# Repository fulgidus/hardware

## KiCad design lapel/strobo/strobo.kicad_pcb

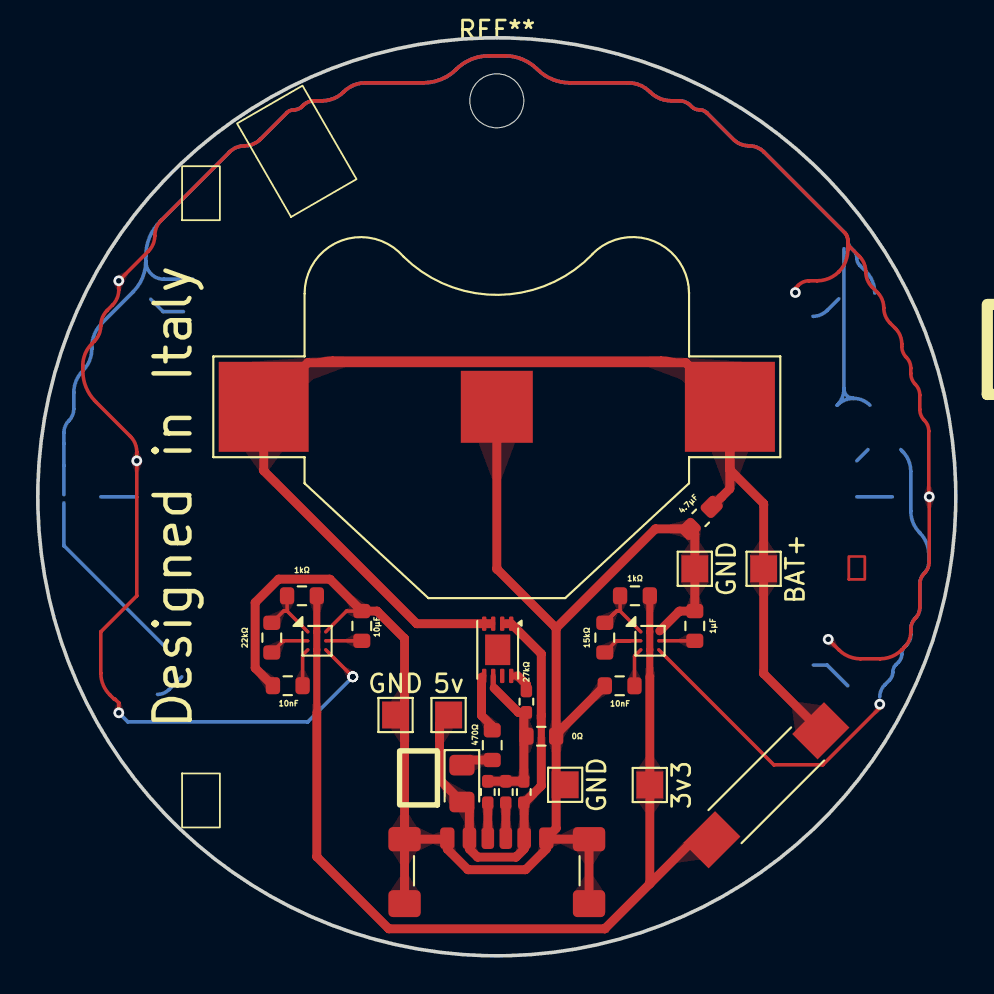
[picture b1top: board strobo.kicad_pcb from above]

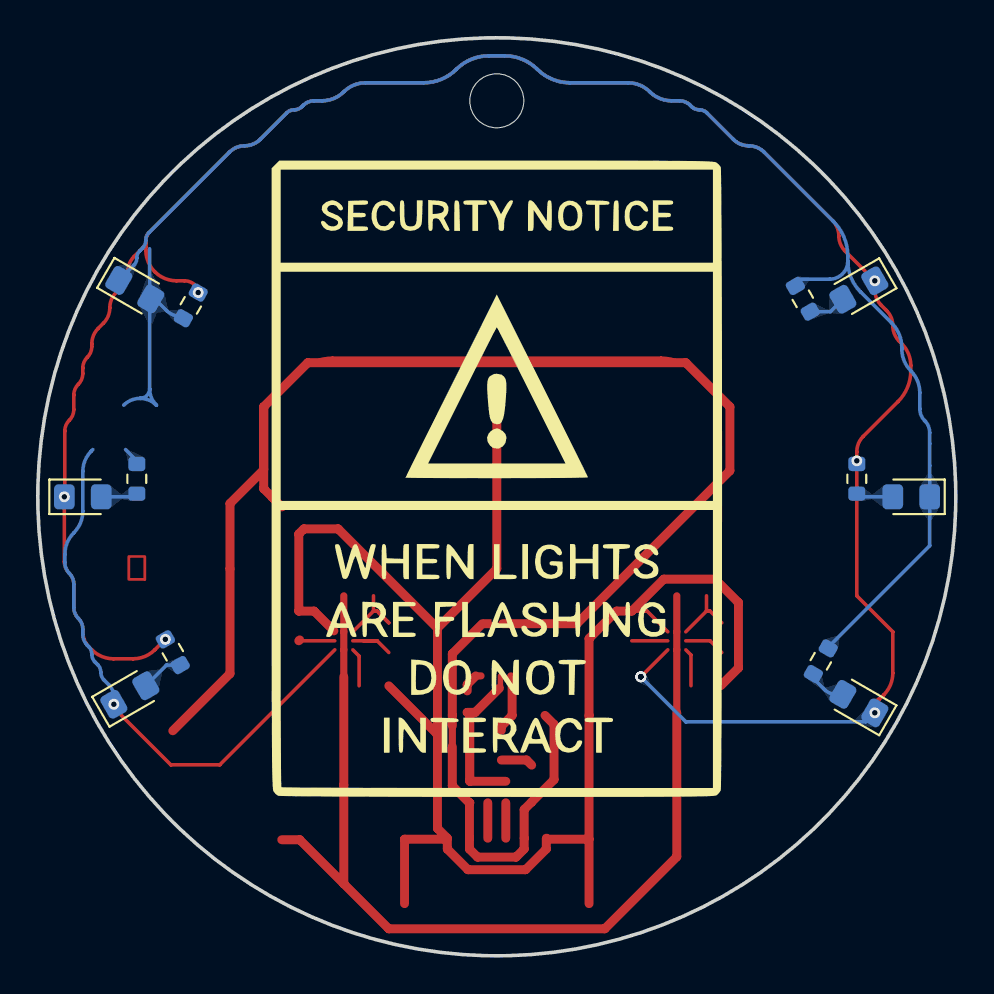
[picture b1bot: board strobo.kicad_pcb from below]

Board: 2 copper layers, 51.0 x 51.0 mm, 35 parts (13 on the bottom side), 25 nets.

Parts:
BT1: 3.7; BatteryHolder_Multicomp_BC-2001_1x2032
B_{1}: 0Ω; R_0603_1608Metric
C1: 4.7µF; R_0402_1005Metric_Pad0.72x0.64mm_HandSolder
C2: 4.7µF; C_0603_1608Metric_Pad1.08x0.95mm_HandSolder
C3: 10µF; R_0603_1608Metric
C4, C6: 10nF; R_0603_1608Metric
C5: 1µF; R_0603_1608Metric
D1, D2, D3, D4, D5, D6, D7: LED; LED_0805_2012Metric_Pad1.15x1.40mm_HandSolder
Image: LOGO
J1: USB-C; USB_C_Receptacle_GCT_USB4135-GF-A_6P_TopMnt_Horizontal
R1, R2: 5.1kΩ; R_0402_1005Metric_Pad0.72x0.64mm_HandSolder
R3: 27kΩ; R_0402_1005Metric_Pad0.72x0.64mm_HandSolder
R4: 470Ω; R_0603_1608Metric
R5, R7, R9, R10, R11, R12, R13, R14: 1kΩ; R_0603_1608Metric
R6: 22kΩ; R_0603_1608Metric
R8: 15kΩ; R_0603_1608Metric
SW1: 0.001; SW_SPST_REED_CT05-XXXX-G1
U2: MCP73831-2-MC; DFN-8-1EP_3x2mm_P0.5mm_EP1.7x1.4mm
U3, U4: LMC555xTP; Texas_DSBGA-8_1.43x1.41mm_Layout3x3_P0.5mm

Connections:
+3.3V: R5.1, R7.1, SW1.2 (B), U3.A2 (VCC), U3.C2 (~RST), U4.A2 (VCC), U4.C2 (~RST)
GND: BT1.2 (-), B_{1}.1, B_{1}.2, C1.1, C2.2, C3.2, C4.1, C5.2, C6.1, J1.A12 (GND), J1.B12 (GND), J1.SH (SHIELD), R1.2, R2.2, R3.1, U2.6 (V_{SS}), U3.A3 (GND), U4.A3 (GND)
unnamed: BT1.1 (+), C2.1, SW1.1 (A), U2.3 (V_{BAT}), U2.4 (V_{BAT})
unnamed: C1.2, D1.2 (A), J1.A9 (VBUS), J1.B9 (VBUS), U2.1 (V_{DD}), U2.2 (V_{DD})
unnamed: D1.1 (K), R4.1
unnamed: D2.2 (A), R9.1
unnamed: D2.1 (K), D4.1 (K), D5.1 (K), R10.2, R13.2, R14.2, U4.C3 (OUT)
unnamed: D3.2 (A), R10.1
unnamed: D3.1 (K), D6.1 (K), D7.1 (K), R9.2, R11.2, R12.2, U3.C3 (OUT)
unnamed: D4.2 (A), R11.1
unnamed: D5.2 (A), R12.1
unnamed: D6.2 (A), R13.1
unnamed: D7.2 (A), R14.1
unnamed: J1.A5 (CC1), R2.1
unnamed: J1.B5 (CC2), R1.1
unnamed: R3.2, U2.8 (PROG)
unnamed: R4.2, U2.5 (STAT)
unnamed: C4.2, U3.C1 (CONT)
unnamed: R5.2, R6.1, U3.A1 (DISCH)
unnamed: R6.2, U3.B1 (THRES)
unnamed: C3.1, U3.B3 (TRIG)
unnamed: C6.2, U4.C1 (CONT)
unnamed: R7.2, R8.1, U4.A1 (DISCH)
unnamed: R8.2, U4.B1 (THRES)
unnamed: C5.1, U4.B3 (TRIG)

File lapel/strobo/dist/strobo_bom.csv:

"Id";"Designator";"Footprint";"Quantity";"Designation";"Supplier and ref";
1;"BT1";"BatteryHolder_Multicomp_BC-2001_1x2032";1;"LIR2032";;;
2;"C1, C2";"C_0805_2012Metric";2;"4.7µF";;;
3;"C3";"C_0805_2012Metric_Pad1.18x1.45mm_HandSolder";1;"10µF";;;
4;"C4, C6";"C_0805_2012Metric_Pad1.18x1.45mm_HandSolder";2;"10nF";;;
5;"C5";"C_0805_2012Metric_Pad1.18x1.45mm_HandSolder";1;"1µF";;;
6;"D1, D2, D3, D4, D5, D6, D7";"LED_0805_2012Metric_Pad1.15x1.40mm_HandSolder";7;"LED";;;
7;"J1";"USB_C_Receptacle_GCT_USB4125-xx-x-0190_6P_TopMnt_Horizontal";1;"USB_C_Receptacle_PowerOnly_6P";;;
8;"R1";"R_0805_2012Metric_Pad1.20x1.40mm_HandSolder";1;"5.1kΩ";;;
9;"R2";"C_0805_2012Metric_Pad1.18x1.45mm_HandSolder";1;"5.1kΩ";;;
10;"R3";"C_0805_2012Metric_Pad1.18x1.45mm_HandSolder";1;"27kΩ";;;
11;"R4, R5, R7, R9, R10, R11, R12, R13, R14";"R_0805_2012Metric_Pad1.20x1.40mm_HandSolder";9;"1kΩ";;;
12;"R6";"R_0805_2012Metric_Pad1.20x1.40mm_HandSolder";1;"22kΩ";;;
13;"R8";"R_0805_2012Metric_Pad1.20x1.40mm_HandSolder";1;"15kΩ";;;
14;"SW1";"SW_Slide_SPDT_Angled_CK_OS102011MA1Q";1;"SW_SPDT";;;
15;"U1";"SOIC-14_3.9x8.7mm_P1.27mm";1;"ICM7556";;;
16;"U2";"DFN-8-1EP_3x2mm_P0.5mm_EP1.7x1.4mm";1;"MCP73831-2-MC";;;

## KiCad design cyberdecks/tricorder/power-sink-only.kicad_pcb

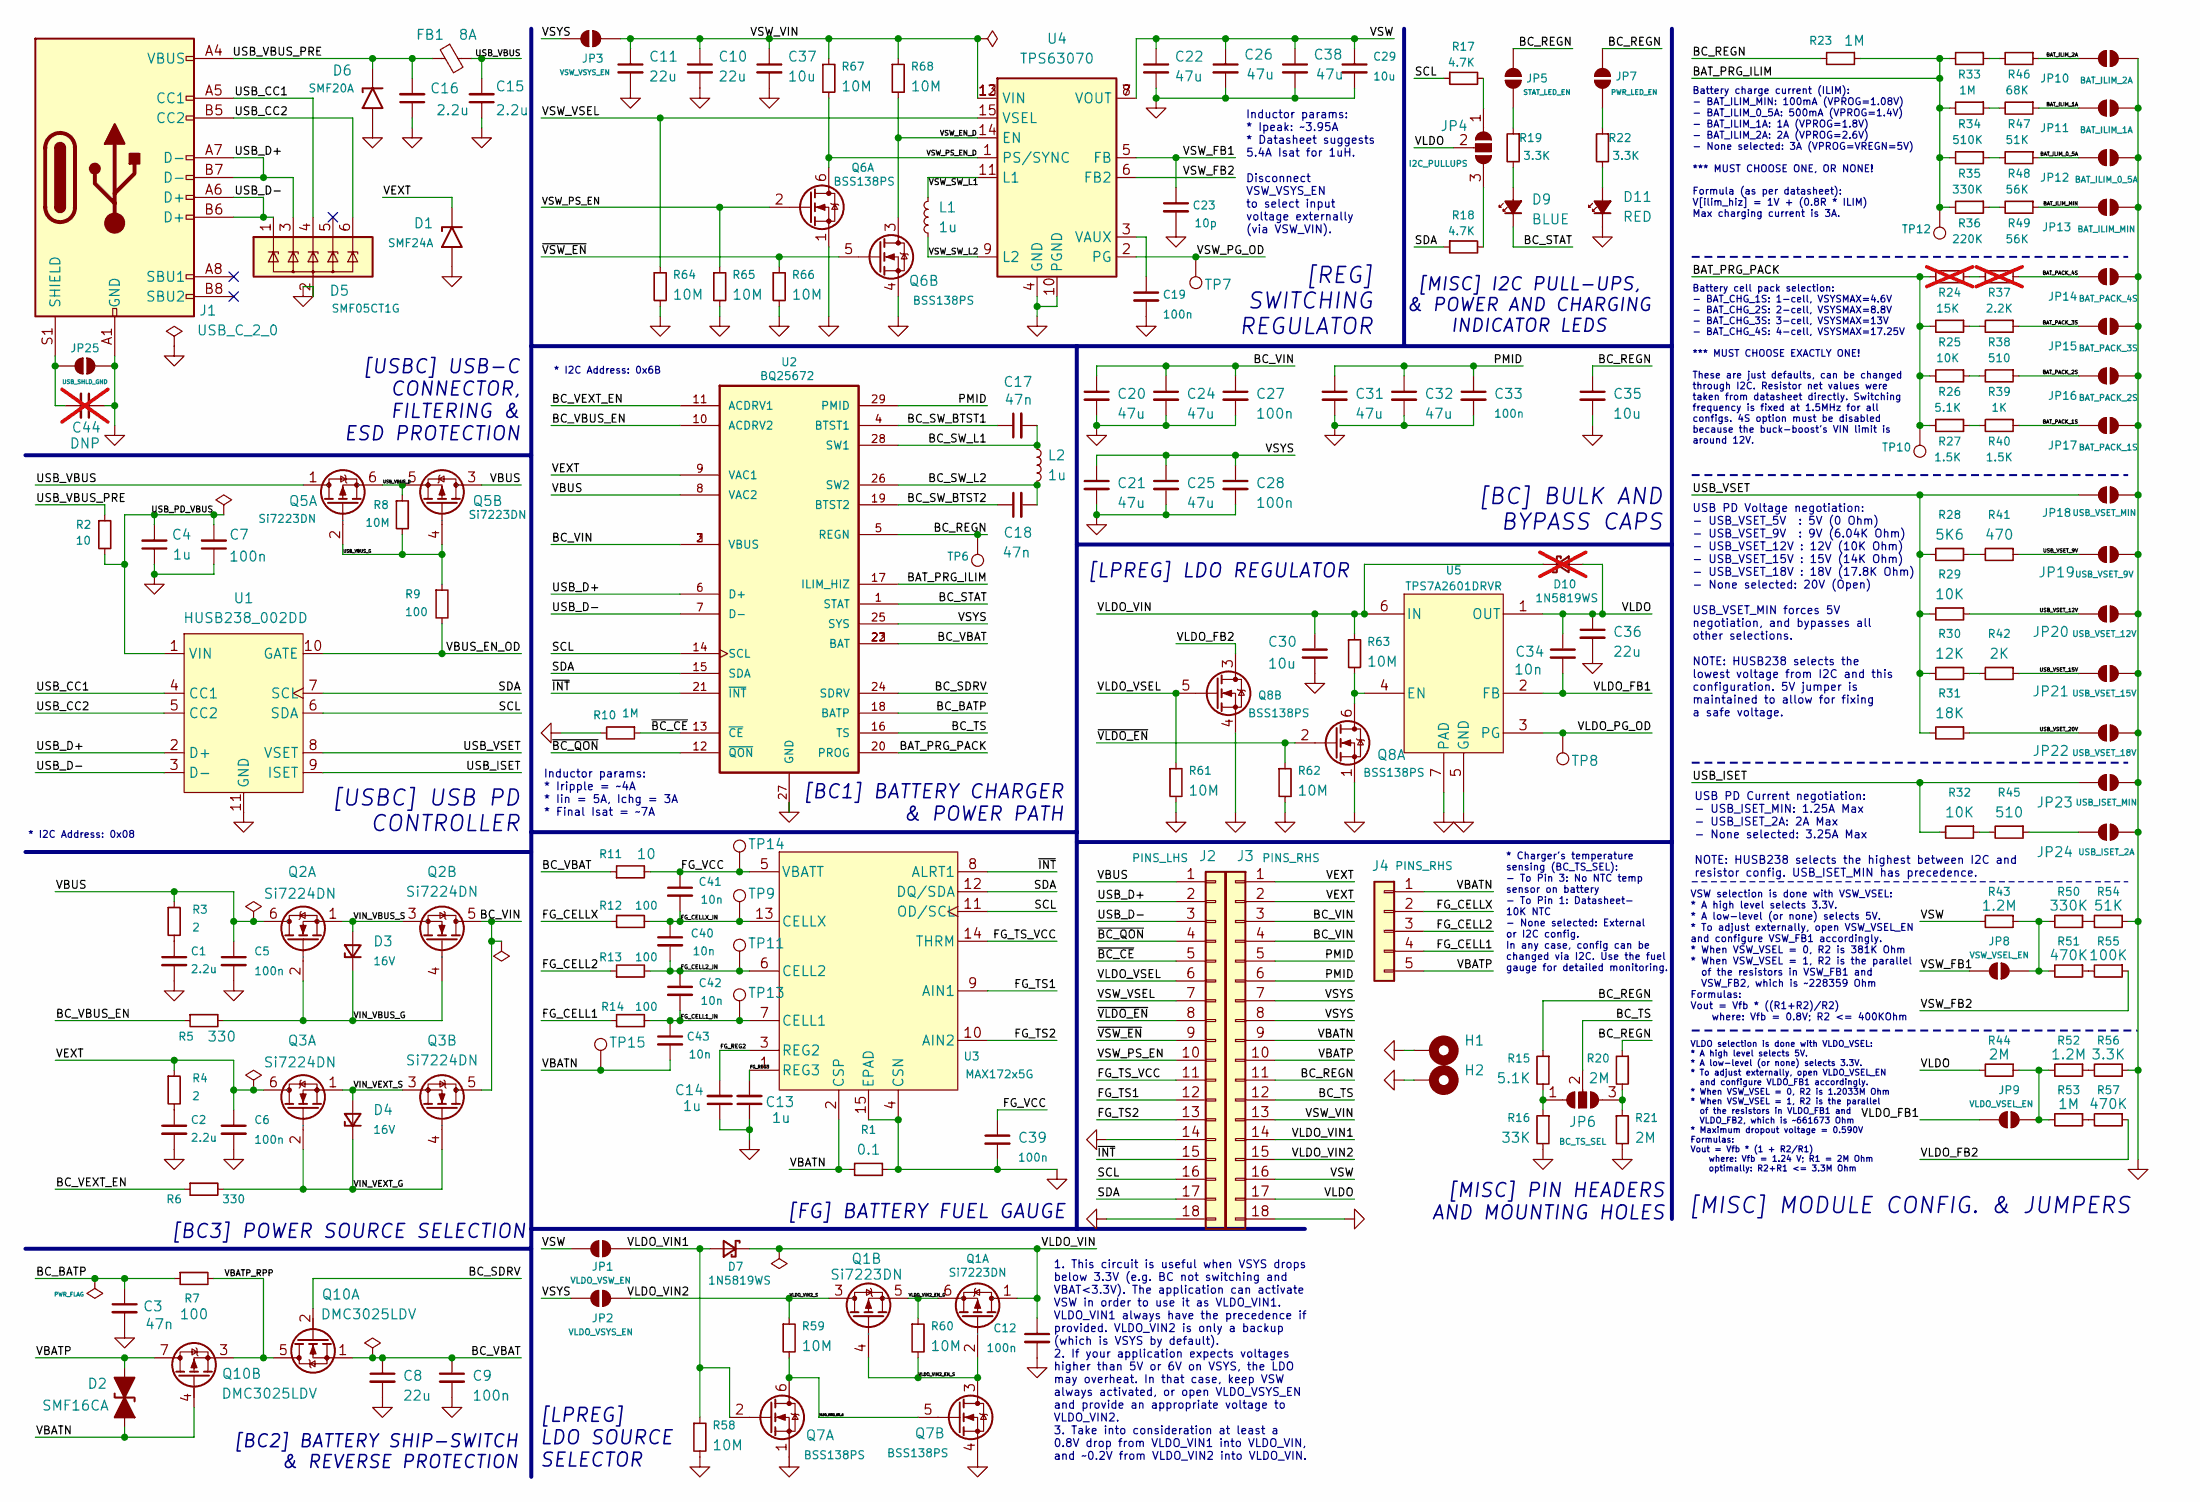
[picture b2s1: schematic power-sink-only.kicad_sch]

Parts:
C1, C2: 2.2u; C_0805_2012Metric
C3, C17, C18: 47n; C_0402_1005Metric
C4, C13, C14: 1u; C_0402_1005Metric
C5, C6, C7, C9, C12, C19, C27, C28, C33, C39: 100n; C_0402_1005Metric
C8, C10, C11, C36: 22u; C_0805_2012Metric
C15, C16: 2.2u; C_0603_1608Metric
C20, C21, C22, C24, C25, C26, C31, C32, C38: 47u; C_0805_2012Metric
C23: 10p; C_0402_1005Metric
C29, C37: 10u; C_0603_1608Metric
C30, C35: 10u; C_0805_2012Metric
C34, C40, C41, C42, C43: 10n; C_0402_1005Metric
C44: DNP; C_0603_1608Metric; not fitted
D1: SMF24A; D_SMF
D2: SMF16CA; D_SOD-123F
D3, D4: 16V; D_SOD-523
D5: SMF05CT1G; SOT-23-6
D6: SMF20A; D_SMF
D7: 1N5819WS; D_SOD-323
D9: BLUE; LED_0603_1608Metric
D10: 1N5819WS; D_SOD-323; not fitted
D11: RED; LED_0603_1608Metric
FB1: 8A; L_1210_3225Metric
H1, H2: MountingHole_Pad; MountingHole_2.2mm_M2_DIN965_Pad_TopBottom
J1: USB_C_2_0; USB_C_Receptacle_GCT_USB4105-xx-A_16P_TopMnt_Horizontal
J2: PINS_LHS; PinHeader_1x18_P2.54mm_Vertical
J3: PINS_RHS; PinHeader_1x18_P2.54mm_Vertical
J4: PINS_RHS; PinHeader_1x05_P2.54mm_Vertical
JP1: VLDO_VSW_EN; SolderJumper-2_P1.3mm_Open_Pad1.0x1.5mm
JP2: VLDO_VSYS_EN; SolderJumper-2_P1.3mm_Open_Pad1.0x1.5mm
JP3: VSW_VSYS_EN; SolderJumper-2_P1.3mm_Open_Pad1.0x1.5mm
JP4: I2C_PULLUPS; SolderJumper-3_P1.3mm_Open_Pad1.0x1.5mm
JP5: STAT_LED_EN; SolderJumper-2_P1.3mm_Open_Pad1.0x1.5mm
JP6: BC_TS_SEL; SolderJumper-3_P1.3mm_Open_Pad1.0x1.5mm
JP7: PWR_LED_EN; SolderJumper-2_P1.3mm_Open_Pad1.0x1.5mm
JP8: VSW_VSEL_EN; SolderJumper-2_P1.3mm_Open_Pad1.0x1.5mm
JP9: VLDO_VSEL_EN; SolderJumper-2_P1.3mm_Open_Pad1.0x1.5mm
JP10: BAT_ILIM_2A; SolderJumper-2_P1.3mm_Open_Pad1.0x1.5mm
JP11: BAT_ILIM_1A; SolderJumper-2_P1.3mm_Open_Pad1.0x1.5mm
JP12: BAT_ILIM_0_5A; SolderJumper-2_P1.3mm_Open_Pad1.0x1.5mm
JP13: BAT_ILIM_MIN; SolderJumper-2_P1.3mm_Open_Pad1.0x1.5mm
JP14: BAT_PACK_4S; SolderJumper-2_P1.3mm_Open_Pad1.0x1.5mm
JP15: BAT_PACK_3S; SolderJumper-2_P1.3mm_Open_Pad1.0x1.5mm
JP16: BAT_PACK_2S; SolderJumper-2_P1.3mm_Open_Pad1.0x1.5mm
JP17: BAT_PACK_1S; SolderJumper-2_P1.3mm_Open_Pad1.0x1.5mm
JP18: USB_VSET_MIN; SolderJumper-2_P1.3mm_Open_Pad1.0x1.5mm
JP19: USB_VSET_9V; SolderJumper-2_P1.3mm_Open_Pad1.0x1.5mm
JP20: USB_VSET_12V; SolderJumper-2_P1.3mm_Open_Pad1.0x1.5mm
JP21: USB_VSET_15V; SolderJumper-2_P1.3mm_Open_Pad1.0x1.5mm
JP22: USB_VSET_18V; SolderJumper-2_P1.3mm_Open_Pad1.0x1.5mm
JP23: USB_ISET_MIN; SolderJumper-2_P1.3mm_Open_Pad1.0x1.5mm
JP24: USB_ISET_2A; SolderJumper-2_P1.3mm_Open_Pad1.0x1.5mm
JP25: USB_SHLD_GND; SolderJumper-2_P1.3mm_Open_Pad1.0x1.5mm
L1, L2: 1u; L_Changjiang_FXL0530
Q1, Q5: Si7223DN; Vishay_PowerPAK_1212-8_Dual
Q2, Q3: Si7224DN; Vishay_PowerPAK_1212-8_Dual
Q6, Q7, Q8: BSS138PS; SOT-363_SC-70-6
Q10: DMC3025LDV; Diodes_PowerDI3333-8_UXC_3.3x3.3mm_P0.65mm
R1: 0.1; R_1210_3225Metric
R2: 10; R_0402_1005Metric
R3: 2; R_0603_1608Metric
R4: 2; R_0402_1005Metric
R5, R6: 330; R_0402_1005Metric
R7, R9: 100; R_0402_1005Metric
R8, R58, R59, R60, R61, R62, R63, R64, R65, R66, R67, R68: 10M; R_0402_1005Metric
R10, R23, R33: 1M; R_0402_1005Metric
R11: 10; R_0603_1608Metric
R12, R13, R14: 100; R_0603_1608Metric
R15, R26: 5.1K; R_0402_1005Metric
R16: 33K; R_0402_1005Metric
R17, R18: 4.7K; R_0402_1005Metric
R19, R22: 3.3K; R_0402_1005Metric
R20, R21: 2M; R_0402_1005Metric
R24: 15K; R_0402_1005Metric; not fitted
R25: 10K; R_0402_1005Metric
R27, R40: 1.5K; R_0402_1005Metric
R28: 5K6; R_0402_1005Metric; LCSC C25908
R29: 10K; R_0402_1005Metric; LCSC C25744
R30: 12K; R_0402_1005Metric; LCSC C25752
R31: 18K; R_0402_1005Metric; LCSC C25762
R32: 10K; R_0402_1005Metric; LCSC C25908
R34: 510K; R_0402_1005Metric
R35: 330K; R_0402_1005Metric
R36: 220K; R_0402_1005Metric
R37: 2.2K; R_0402_1005Metric; not fitted
R38: 510; R_0402_1005Metric
R39: 1K; R_0402_1005Metric
R41: 470; R_0402_1005Metric; LCSC C25117
R42: 2K; R_0402_1005Metric; LCSC C4109
R43, R52: 1.2M; R_0402_1005Metric; LCSC C25741
R44: 2M; R_0402_1005Metric; LCSC C25741
R45: 510; R_0402_1005Metric; LCSC C25117
R46: 68K; R_0402_1005Metric
R47: 51K; R_0402_1005Metric
R48, R49: 56K; R_0402_1005Metric
R50: 330K; R_0402_1005Metric; LCSC C25741
R51, R57: 470K; R_0402_1005Metric; LCSC C25741
R53: 1M; R_0402_1005Metric; LCSC C25741
R54: 51K; R_0402_1005Metric; LCSC C25741
R55: 100K; R_0402_1005Metric; LCSC C25741
R56: 3.3K; R_0402_1005Metric; LCSC C25741
TP6, TP7, TP8, TP9, TP10, TP11, TP12, TP13, TP14, TP15: TestPoint; TestPoint_Pad_1.0x1.0mm
U1: HUSB238_002DD; DFN-10-1EP_3x3mm_P0.5mm_EP1.7x2.5mm; JLCPCB C7471904
U2: BQ25672; SPECIFIC_BQ25672RQMR; JLCPCB C3682029
U3: MAX172x5G; SPECIFIC_MAX172x5G_21-0137_T1433-2C_MXM
U4: TPS63070; SPECIFIC_TPS63070_RNM0015A
U5: TPS7A2601DRVR; SPECIFIC_TPS7A2601DRVR_NoThermalVias

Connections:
/BAT_ILIM_0_5A: JP12.1 (A), R48.1
/BAT_ILIM_1A: JP11.1 (A), R47.1
/BAT_ILIM_2A: JP10.1 (A), R46.1
/BAT_ILIM_MIN: JP13.1 (A), R49.1
/BAT_PACK_1S: JP17.1 (A), R40.1
/BAT_PACK_2S: JP16.1 (A), R39.1
/BAT_PACK_3S: JP15.1 (A), R38.1
/BAT_PACK_4S: JP14.1 (A), R37.1
/BAT_PRG_ILIM: R23.1, R33.2, R34.2, R35.2, R36.2, TP12.1, U2.17 (ILIM_HIZ)
/BAT_PRG_PACK: R24.2, R25.2, R26.2, R27.2, TP10.1, U2.20 (PROG)
/BC_BATP: C3.1, R7.1, U2.18 (BATP)
/BC_REGN: C35.1, J3.11, JP5.2 (B), JP7.2 (B), R15.1, R20.1, R23.2, TP6.1, U2.5 (REGN)
/BC_SDRV: Q10.2 (G), U2.24 (SDRV)
/BC_STAT: D9.1 (K), U2.1 (STAT)
/BC_SW_BTST1: C17.1, U2.4 (BTST1)
/BC_SW_BTST2: C18.1, U2.19 (BTST2)
/BC_SW_L1: C17.2, L2.1, U2.28 (SW1)
/BC_SW_L2: C18.2, L2.2, U2.26 (SW2)
/BC_TS: J3.12, JP6.2 (C), U2.16 (TS)
/BC_VBAT: C8.1, C9.1, Q10.1 (S), R11.1, U2.22 (BAT), U2.23 (BAT)
/BC_VBUS_EN: R5.1, U2.10 (ACDRV2)
/BC_VEXT_EN: R6.1, U2.11 (ACDRV1)
/BC_VIN: C20.1, C24.1, C27.1, J3.3, J3.4, Q2.5 (D), Q3.5 (D), U2.2 (VBUS), U2.3 (VBUS)
/FG_CELL1: J4.4, R14.1
/FG_CELL1_IN: C42.2, C43.1, R14.2, TP13.1, U3.7 (CELL1)
/FG_CELL2: J4.3, R13.1
/FG_CELL2_IN: C40.2, C42.1, R13.2, TP11.1, U3.6 (CELL2)
/FG_CELLX: J4.2, R12.1
/FG_CELLX_IN: C40.1, C41.2, R12.2, TP9.1, U3.13 (CELLX)
/FG_REG2: C14.2, U3.3 (REG2)
/FG_REG3: C13.2, U3.1 (REG3)
/FG_TS1: J2.12, U3.9 (AIN1)
/FG_TS2: J2.13, U3.10 (AIN2)
/FG_TS_VCC: J2.11, U3.14 (THRM)
/FG_VCC: C39.1, C41.1, R11.2, TP14.1, U3.5 (VBATT)
/PMID: C31.1, C32.1, C33.1, J3.5, J3.6, U2.29 (PMID)
/SCL: J2.16, R17.1, U1.6 (SDA), U2.14 (SCL), U3.11 (OD/SCL)
/SDA: J2.17, R18.1, U1.7 (SCL), U2.15 (SDA), U3.12 (DQ/SDA)
/USB_CC1: D5.4 (IO3), J1.A5 (CC1), U1.4 (CC1)
/USB_CC2: D5.6 (IO5), J1.B5 (CC2), U1.5 (CC2)
/USB_D+: D5.3 (IO2), J1.A7 (D-), J1.B7 (D-), J2.2, U1.2 (D+), U2.6 (D+)
/USB_D-: D5.1 (IO1), J1.A6 (D+), J1.B6 (D+), J2.3, U1.3 (D-), U2.7 (D-)
/USB_ISET: JP23.1 (A), R32.2, U1.9 (ISET)
/USB_PD_VBUS: C4.2, C7.2, R2.2, U1.1 (VIN)
/USB_VBUS: C15.2, FB1.2, Q5.1 (D)
/USB_VBUS_D: Q5.5 (S), Q5.6 (S), R8.1
/USB_VBUS_G: Q5.2 (G), Q5.4 (G), R8.2, R9.1
/USB_VBUS_PRE: C16.2, D6.1 (A1), FB1.1, J1.A4 (VBUS), J1.A9 (VBUS), J1.B4 (VBUS), J1.B9 (VBUS), R2.1
/USB_VSET: JP18.1 (A), R28.2, R29.2, R30.2, R31.2, U1.8 (VSET)
/USB_VSET_9V: JP19.1 (A), R41.1
/USB_VSET_12V: JP20.1 (A), R29.1
/USB_VSET_15V: JP21.1 (A), R42.1
/USB_VSET_20V: JP22.1 (A), R31.1
/VBATN: C43.2, D2.1 (A1), J3.9, J4.1, Q10.4 (G), R1.1, TP15.1, U3.2 (CSP)
/VBATP: D2.2 (A2), J3.10, J4.5, Q10.7 (D)
/VBATP_RPP: Q10.3 (S), Q10.5 (D), R7.2
/VBUS: C5.1, J2.1, Q2.6 (D), Q5.3 (D), R3.1, U2.8 (VAC2)
/VBUS_EN_OD: R9.2, U1.10 (GATE)
/VEXT: C6.1, D1.1 (A1), J3.1, J3.2, Q3.6 (D), R4.1, U2.9 (VAC1)
/VIN_VBUS_G: D3.1 (K), Q2.2 (G), Q2.4 (G), R5.2
/VIN_VBUS_S: D3.2 (A), Q2.1 (S), Q2.3 (S)
/VIN_VEXT_G: D4.1 (K), Q3.2 (G), Q3.4 (G), R6.2
/VIN_VEXT_S: D4.2 (A), Q3.1 (S), Q3.3 (S)
/VLDO: C34.1, C36.1, D10.2 (A), J3.17, JP4.2 (C), R44.2, U5.1 (OUT)
/VLDO_FB1: C34.2, JP9.1 (A), U5.2 (FB)
/VLDO_FB2: Q8.3 (D), R57.1
/VLDO_PG_OD: TP8.1, U5.3 (PG)
/VLDO_VIN: C12.1, C30.1, D7.1 (K), D10.1 (K), Q1.1 (D), R63.1, U5.6 (IN)
/VLDO_VIN1: D7.2 (A), J3.14, JP1.2 (B), Q7.2 (G), R58.1
/VLDO_VIN2: J3.15, JP2.2 (B), Q1.3 (D), R59.1
/VLDO_VIN2_EN_G: Q1.5 (S), Q1.6 (S), Q7.5 (G), Q7.6 (D), R59.2, R60.1
/VLDO_VIN2_EN_S: Q1.2 (G), Q1.4 (G), Q7.3 (D), R60.2
/VLDO_VSEL: J2.6, Q8.5 (G), R61.1
/VSW: C22.1, C26.1, C29.1, C38.1, J3.16, JP1.1 (A), R43.2, U4.7 (VOUT), U4.8 (VOUT)
/VSW_EN_D: Q6.3 (D), R68.2, U4.14 (EN)
/VSW_FB1: C23.1, JP8.1 (A), U4.5 (FB)
/VSW_FB2: R55.1, U4.6 (FB2)
/VSW_PG_OD: TP7.1, U4.2 (PG)
/VSW_PS_EN: J2.10, Q6.2 (G), R65.1
/VSW_PS_EN_D: Q6.6 (D), R67.2, U4.1 (PS/SYNC)
/VSW_SW_L1: L1.2, U4.11 (L1)
/VSW_SW_L2: L1.1, U4.9 (L2)
/VSW_VIN: C10.1, C11.1, C37.1, J3.13, JP3.2 (B), R67.1, R68.1, U4.12 (VIN), U4.13 (VIN)
/VSW_VSEL: J2.7, R64.1, U4.15 (VSEL)
/VSYS: C21.1, C25.1, C28.1, J3.7, J3.8, JP2.1 (A), JP3.1 (A), U2.25 (SYS)
/~BC_CE: J2.5, R10.1, U2.13 (~CE)
/~BC_QON: J2.4, U2.12 (~QON)
/~INT: J2.15, U2.21 (~INT), U3.8 (ALRT1)
/~VLDO_EN: J2.8, Q8.2 (G), R62.1
/~VSW_EN: J2.9, Q6.5 (G), R66.1
GND: C1.2, C2.2, C3.2, C4.1, C5.2, C6.2, C7.1, C8.2, C9.2, C10.2, C11.2, C12.2, C13.1, C14.1, C15.1, C16.1, C19.2, C20.2, C21.2, C22.2, C23.2, C24.2, C25.2, C26.2, C27.2, C28.2, C29.2, C30.2, C31.2, C32.2, C33.2, C35.2, C36.2, C37.2, C38.2, C39.2, C44.1, D1.2 (A2), D5.2 (GND), D6.2 (A2), D11.1 (K), H1.1, H2.1, J1.A1 (GND), J1.A12 (GND), J1.B1 (GND), J1.B12 (GND), J2.14, J2.18, J3.18, JP10.2 (B), JP11.2 (B), JP12.2 (B), JP13.2 (B), JP14.2 (B), JP15.2 (B), JP16.2 (B), JP17.2 (B), JP18.2 (B), JP19.2 (B), JP20.2 (B), JP21.2 (B), JP22.2 (B), JP23.2 (B), JP24.2 (B), JP25.2 (B), Q6.1 (S), Q6.4 (S), Q7.1 (S), Q7.4 (S), Q8.1 (S), Q8.4 (S), R1.2, R10.2, R16.2, R21.2, R54.1, R56.1, R58.2, R61.2, R62.2, R64.2, R65.2, R66.2, U1.11 (GND), U2.27 (GND), U3.4 (CSN), U3.15 (EPAD), U4.4 (GND), U4.10 (PGND), U5.5 (GND), U5.7 (PAD)
unnamed: C1.1, R3.2
unnamed: C2.1, R4.2
unnamed: D9.2 (A), R19.2
unnamed: D11.2 (A), R22.2
unnamed: C44.2, J1.S1 (SHIELD), JP25.1 (A)
unnamed: JP4.1 (A), R17.2
unnamed: JP4.3 (B), R18.2
unnamed: JP5.1 (A), R19.1
unnamed: JP6.1 (A), R15.2, R16.1
unnamed: JP6.3 (B), R20.2, R21.1
unnamed: JP7.1 (A), R22.1
unnamed: JP8.2 (B), R43.1, R50.2, R51.2
unnamed: JP9.2 (B), R44.1, R52.2, R53.2
unnamed: JP24.1 (A), R45.1
unnamed: Q8.6 (D), R63.2, U5.4 (EN)
unnamed: R24.1, R37.2
unnamed: R25.1, R38.2
unnamed: R26.1, R39.2
unnamed: R27.1, R40.2
unnamed: R28.1, R41.2
unnamed: R30.1, R42.2
unnamed: R32.1, R45.2
unnamed: R33.1, R46.2
unnamed: R34.1, R47.2
unnamed: R35.1, R48.2
unnamed: R36.1, R49.2
unnamed: R50.1, R54.2
unnamed: R51.1, R55.2
unnamed: R52.1, R56.2
unnamed: R53.1, R57.2
unnamed: C19.1, U4.3 (VAUX)

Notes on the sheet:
[BC3] POWER SOURCE SELECTION
USB PD Current negotiation: - USB_ISET_MIN: 1.25A Max - USB_ISET_2A: 2A Max - None selected: 3.25A Max NOTE: HUSB238 selects the highest between I2C and resistor config. USB_ISET_MIN has precedence.
[USBC] USB PD CONTROLLER
* I2C Address: 0x08
[BC1] BATTERY CHARGER & POWER PATH
[FG] BATTERY FUEL GAUGE
USB PD Voltage negotiation: - USB_VSET_5V : 5V (0 Ohm) - USB_VSET_9V : 9V (6.04K Ohm) - USB_VSET_12V : 12V (10K Ohm) - USB_VSET_15V : 15V (14K Ohm) - USB_VSET_18V : 18V (17.8K Ohm) - None selected: 20V (Open) USB_VSET_MIN forces 5V negotiation, and bypasses all other selections. NOTE: HUSB238 selec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
Battery cell pack selection: - BAT_CHG_1S: 1-cell, VSYSMAX=4.6V - BAT_CHG_2S: 2-cell, VSYSMAX=8.8V - BAT_CHG_3S: 3-cell, VSYSMAX=13V - BAT_CHG_4S: 4-cell, VSYSMAX=17.25V *** MUST CHOOSE EXACTLY ONE! These are just defaults, can be changed through I2C. Resistor net values were taken from datasheet d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
[BC2] BATTERY SHIP-SWITCH & REVERSE PROTECTION
[MISC] PIN HEADERS AND MOUNTING HOLES
Inductor params: * Ipeak: ~3.95A * Datasheet suggests 5.4A Isat for 1uH. Disconnect VSW_VSYS_EN to select input voltage externally (via VSW_VIN).
1. This circuit is useful when VSYS drops below 3.3V (e.g. BC not switching and VBAT<3.3V). The application can activate VSW in order to use it as VLDO_VIN1. VLDO_VIN1 always have the precedence if provided. VLDO_VIN2 is only a backup (which is VSYS by default). 2. If your application expects volta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
[LPREG] LDO REGULATOR
VLDO selection is done with VLDO_VSEL: * A high level selects 5V. * A low-level (or none) selects 3.3V. * To adjust externally, open VLDO_VSEL_EN and configure VLDO_FB1 accordingly. * When VSW_VSEL = 0, R2 is 1.2033M Ohm * When VSW_VSEL = 1, R2 is the parallel of the resistors in VLDO_FB1 and VLDO_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
[MISC] I2C PULL-UPS, & POWER AND CHARGING INDICATOR LEDS
VSW selection is done with VSW_VSEL: * A high level selects 3.3V. * A low-level (or none) selects 5V. * To adjust externally, open VSW_VSEL_EN and configure VSW_FB1 accordingly. * When VSW_VSEL = 0, R2 is 381K Ohm * When VSW_VSEL = 1, R2 is the parallel of the resistors in VSW_FB1 and VSW_FB2, whic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
* I2C Address: 0x6B
* Charger's temperature sensing (BC_TS_SEL): - To Pin 3: No NTC temp sensor on battery - To Pin 1: Datasheet- 10K NTC - None selected: External or I2C config. In any case, config can be changed via I2C. Use the fuel gauge for detailed monitoring.
Battery charge current (ILIM): - BAT_ILIM_MIN: 100mA (VPROG=1.08V) - BAT_ILIM_0_5A: 500mA (VPROG=1.4V) - BAT_ILIM_1A: 1A (VPROG=1.8V) - BAT_ILIM_2A: 2A (VPROG=2.6V) - None selected: 3A (VPROG=VREGN=5V) *** MUST CHOOSE ONE, OR NONE! Formula (as per datasheet): V[ilim_hiz] = 1V + (0.8R * ILIM) Max ch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
[MISC] MODULE CONFIG. & JUMPERS
[LPREG] LDO SOURCE SELECTOR
[BC] BULK AND BYPASS CAPS
Inductor params: * Iripple = ~4A * Iin = 5A, Ichg = 3A * Final Isat = ~7A
[USBC] USB-C CONNECTOR, FILTERING & ESD PROTECTION
[REG] SWITCHING REGULATOR

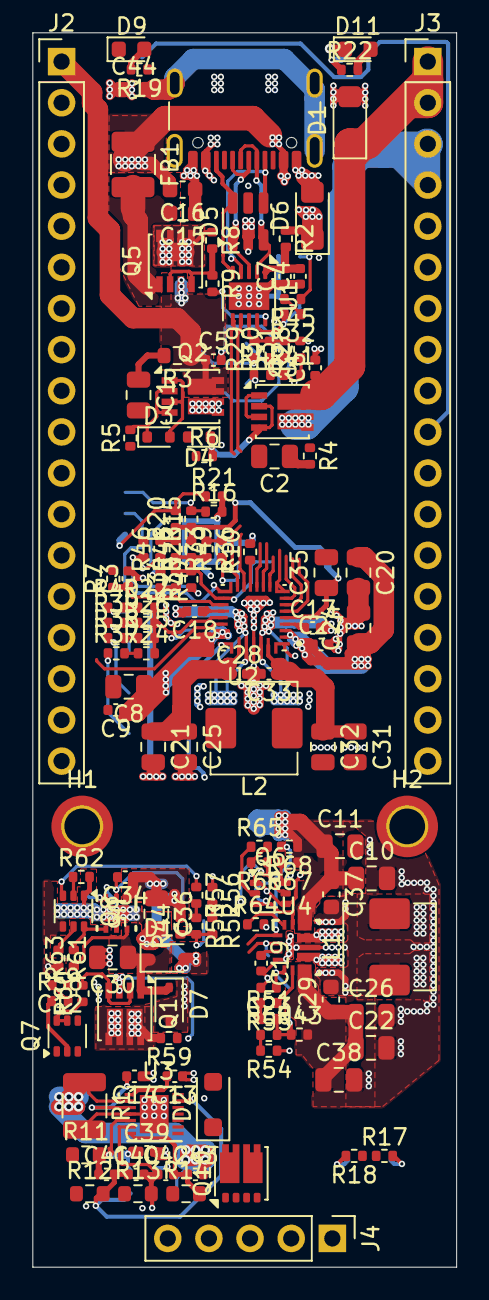
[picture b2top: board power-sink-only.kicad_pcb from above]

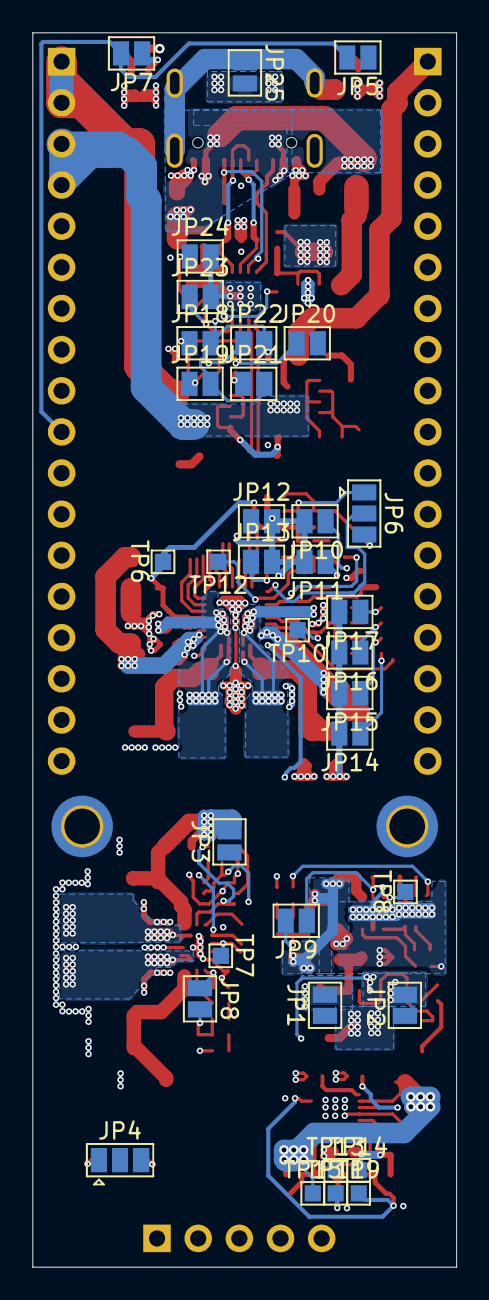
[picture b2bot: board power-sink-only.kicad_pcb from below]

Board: 4 copper layers, 26.2 x 76.2 mm, 179 parts (35 on the bottom side), 122 nets.

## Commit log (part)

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2026-05-20 feat(strobo): route PCB, reposition U1, update design rules
    - Add track segments (GND, CC1, power nets)
    - Move U1 (SOIC-14) to 50,58.5
    - Set min clearance 0.1mm, add track width 1.0mm, via 1.0/0.5mm
    - Add diff pair dims entry
    - Clear component Description fields
    - Remove freerouting.dsn temp files
2026-05-22 feat(strobo): PCB layout, schematic updates, and fabrication outputs
    - Add SW_SPDT symbol to schematic
    - Major PCB layout rework (routing, component placement)
    - Add DRC exclusions with justification notes
    - Configure ngspice simulation workbook
    - Set plot output path to dist/
    - Change dimension units to mm
2026-05-26 Decks'n'stuff
2026-05-26 .gitignore
2026-05-26 libs
2026-05-26 rgb earrings
2026-05-26 cyberdeck
2026-05-26 Add schematic files for Tricorder project
2026-06-15 HexTile first draft
2026-06-16 lint
2026-06-16 svg first draft
2026-06-16 somt images
2026-06-16 pdfs
2026-06-17 docs
2026-06-17 rename docs folder
2026-06-17 new idea for layout
